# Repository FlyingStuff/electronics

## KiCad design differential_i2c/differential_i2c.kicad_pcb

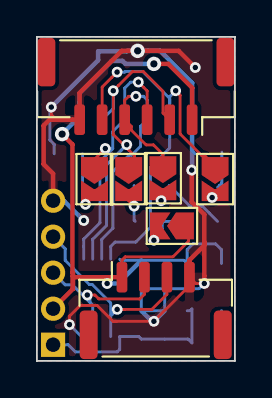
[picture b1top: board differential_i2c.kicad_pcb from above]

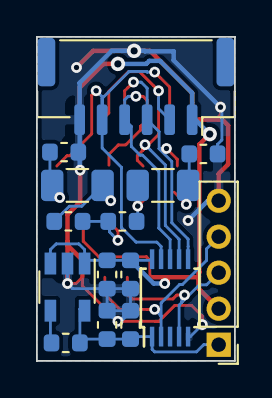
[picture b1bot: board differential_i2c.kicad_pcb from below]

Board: 2 copper layers, 11.0 x 18.0 mm, 22 parts (15 on the bottom side), 15 nets.

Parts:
C1: 1uF; C_0603_1608Metric
C2, C5: 100nF; C_0603_1608Metric
C3: 0.01uF; C_0603_1608Metric
C4: 10uF; C_0603_1608Metric
J1: I2C; JST_GH_SM04B-GHS-TB_1x04-1MP_P1.25mm_Horizontal
J2, J3: I2C_differential; JST_GH_SM06B-GHS-TB_1x06-1MP_P1.25mm_Horizontal
J4: I2C; PinHeader_1x05_P2.00mm_Vertical
JP1, JP2, JP3, JP4, JP5: NC; SolderJumper-2_P1.3mm_Open_TrianglePad1.0x1.5mm
R1, R3, R4, R6: 604; R_0603_1608Metric
R2, R5: 120; R_1206_3216Metric
U1: LT1761-3.3; TSOT-23-5
U2: PCA9615; TSSOP-10_3x3mm_P0.5mm

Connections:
+3V3: C2.1, C3.1, C4.1, J4.1, U1.5, U2.1
+5V: C1.1, C5.1, J1.1, J2.1, J3.1, J4.2, JP3.1, U1.1, U1.3, U2.10
/DI2C_SCLM: J2.3, J3.3, JP2.1, U2.6
/DI2C_SCLP: J2.2, J3.2, JP1.1, U2.7
/DI2C_SDAM: J2.5, J3.5, JP5.1, U2.9
/DI2C_SDAP: J2.4, J3.4, JP4.1, U2.8
/SCL: J1.2, J4.3, U2.4
/SDA: J1.3, J4.4, U2.2
GND: C1.2, C2.2, C4.2, C5.2, J1.4, J2.6, J3.6, J4.5, R3.2, R6.2, U1.2, U2.5
unnamed: C3.2, U1.4
unnamed: JP1.2, R1.2, R2.1
unnamed: JP2.2, R2.2, R3.1
unnamed: JP3.2, R1.1, R4.1
unnamed: JP4.2, R4.2, R5.1
unnamed: JP5.2, R5.2, R6.1

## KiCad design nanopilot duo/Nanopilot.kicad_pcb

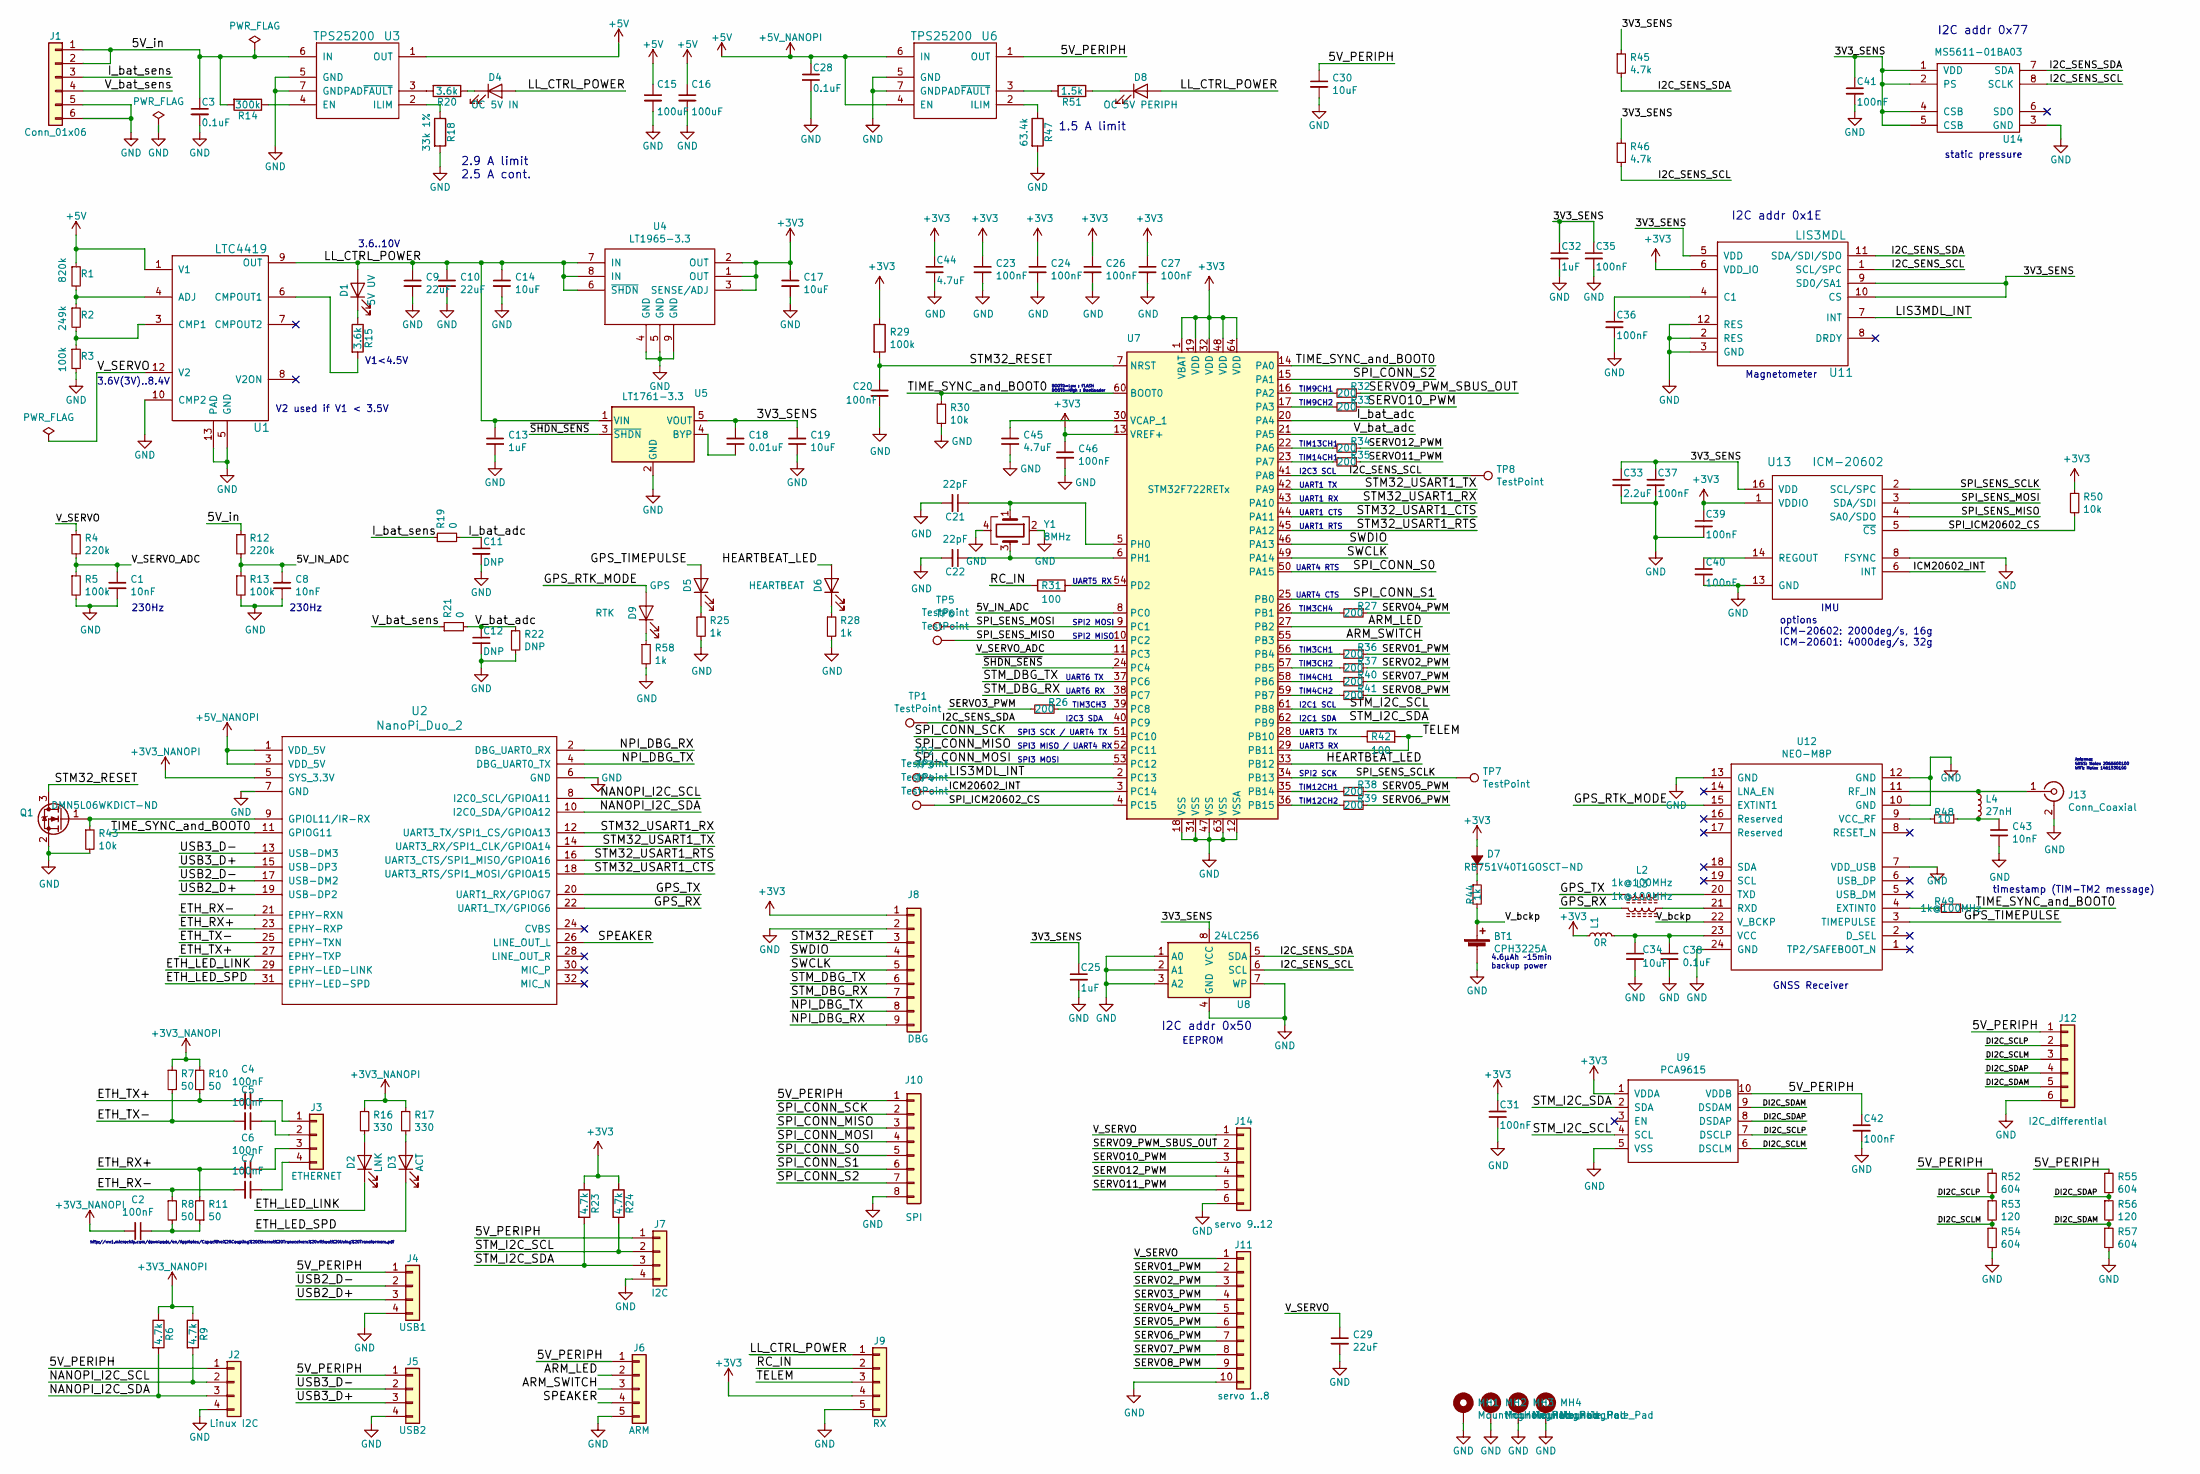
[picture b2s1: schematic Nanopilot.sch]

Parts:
BT1: CPH3225A; Seiko_supercap_CPH3225A
C1, C8, C43: 10nF; C_0603_1608Metric
C2, C4, C5, C6, C7, C20, C23, C24, C26, C27, C31, C35, C36, C37, C39, C40, C41, C42, C46: 100nF; C_0603_1608Metric
C3, C28, C38: 0.1uF; C_0603_1608Metric
C9, C10, C29: 22uF; C_0805_2012Metric
C11, C12: DNP; C_0603_1608Metric
C13, C25, C32: 1uF; C_0603_1608Metric
C14, C17, C19, C30, C34: 10uF; C_0603_1608Metric
C15, C16: 100uF; C_0805_2012Metric
C18: 0.01uF; C_0603_1608Metric
C21, C22: 22pF; C_0603_1608Metric
C33: 2.2uF; C_0603_1608Metric
C44, C45: 4.7uF; C_0603_1608Metric
D1: 5V UV; LED_0603_1608Metric
D2: LNK; LED_0603_1608Metric
D3: ACT; LED_0603_1608Metric
D4: OC 5V IN; LED_0603_1608Metric
D5: GPS; LED_0603_1608Metric
D6: HEARTBEAT; LED_0603_1608Metric
D7: RB751V40T1GOSCT-ND; D_SOD-323; part RB751V40T1GOSCT-ND
D8: OC 5V PERIPH; LED_0603_1608Metric
D9: RTK; LED_0603_1608Metric
J1: Conn_01x06; JST_GH_SM06B-GHS-TB_1x06-1MP_P1.25mm_Horizontal
J2: Linux I2C; JST_GH_SM04B-GHS-TB_1x04-1MP_P1.25mm_Horizontal
J3: ETHERNET; JST_GH_BM04B-GHS-TBT_1x04-1MP_P1.25mm_Vertical
J4: USB1; JST_GH_BM04B-GHS-TBT_1x04-1MP_P1.25mm_Vertical
J5: USB2; JST_GH_SM04B-GHS-TB_1x04-1MP_P1.25mm_Horizontal
J6: ARM; JST_GH_SM05B-GHS-TB_1x05-1MP_P1.25mm_Horizontal
J7: I2C; JST_GH_SM04B-GHS-TB_1x04-1MP_P1.25mm_Horizontal
J8: DBG; Molex_PicoBlade_53398-0971_1x09-1MP_P1.25mm_Vertical
J9: RX; JST_GH_SM05B-GHS-TB_1x05-1MP_P1.25mm_Horizontal
J10: SPI; JST_GH_BM08B-GHS-TBT_1x08-1MP_P1.25mm_Vertical
J11: servo 1..8; JST_GH_SM10B-GHS-TB_1x10-1MP_P1.25mm_Horizontal
J12: I2C_differential; JST_GH_SM06B-GHS-TB_1x06-1MP_P1.25mm_Horizontal
J13: Conn_Coaxial; U.FL_Hirose_U.FL-R-SMT-1_Vertical
J14: servo 9..12; JST_GH_SM06B-GHS-TB_1x06-1MP_P1.25mm_Horizontal
L1: 0R; L_0603_1608Metric
L2, L3: 1k@100MHz; L_0603_1608Metric; digikey 445-8672-1-ND
L4: 27nH; L_0603_1608Metric
MH1, MH2, MH3, MH4: MountingHole_Pad; MountingHole_2.2mm_M2_Pad_Via
Q1: DMN5L06WKDICT-ND; SOT-323_SC-70
R1: 820k; R_0603_1608Metric
R2: 249k; R_0603_1608Metric
R3, R5, R13, R29: 100k; R_0603_1608Metric
R4, R12: 220k; R_0603_1608Metric
R6, R9, R23, R24, R45, R46: 4.7k; R_0603_1608Metric
R7, R8, R10, R11: 50; R_0603_1608Metric
R14: 300k; R_0603_1608Metric
R15, R20: 3.6k; R_0603_1608Metric
R16, R17: 330; R_0603_1608Metric
R18: 33k 1%; R_0603_1608Metric
R19, R21: 0; R_0603_1608Metric
R22: DNP; R_0603_1608Metric
R25, R28, R44, R58: 1k; R_0603_1608Metric
R26, R27, R32, R33, R34, R35, R36, R37, R38, R39, R40, R41: 200; R_0603_1608Metric
R30, R43, R50: 10k; R_0603_1608Metric
R31, R42: 100; R_0603_1608Metric
R47: 63.4k; R_0603_1608Metric
R48: 10; R_0603_1608Metric
R49: 1k@100MHz; R_0603_1608Metric
R51: 1.5k; R_0603_1608Metric
R52, R54, R55, R57: 604; R_0603_1608Metric
R53, R56: 120; R_1206_3216Metric
TP1, TP2, TP3, TP4, TP5, TP6, TP7, TP8: TestPoint; TestPoint_Pad_D1.0mm
U1: LTC4419; MSOP-12-1EP_3x4mm_P0.65mm_EP1.65x2.85mm
U2: NanoPi_Duo_2; nanopi-duo-2
U3, U6: TPS25200; TPS25200_WSON_6
U4: LT1965-3.3; MSOP-8-1EP_3x3mm_P0.65mm_EP1.68x1.88mm
U5: LT1761-3.3; TSOT-23-5
U7: STM32F722RETx; LQFP-64_10x10mm_P0.5mm
U8: 24LC256; MSOP-8_3x3mm_P0.65mm
U9: PCA9615; TSSOP-10_3x3mm_P0.5mm
U11: LIS3MDL; LGA12R50P4X4_200X200X100
U12: NEO-M8P; ublox_NEO
U13: ICM-20602; LGA-16_3x3mm_P0.5mm_LayoutBorder3x5y-ICM-20602
U14: MS5611-01BA03; MS5611-01BA
Y1: 8MHz; Crystal_SMD_Abracon_ABM3C-4Pin_5.0x3.2mm

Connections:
+3V3: C17.1, C23.1, C24.1, C26.1, C27.1, C31.1, C39.1, C44.1, C46.1, D7.2 (A), J8.1, J9.4, L1.1, R23.1, R24.1, R29.1, R50.1, U4.1 (OUT), U4.2 (OUT), U4.3 (SENSE/ADJ), U7.1 (VBAT), U7.13 (VREF+), U7.19 (VDD), U7.32 (VDD), U7.48 (VDD), U7.64 (VDD), U9.1 (VDDA), U11.6 (VDD_IO), U13.1 (VDDIO)
+3V3_NANOPI: C2.2, R6.1, R7.1, R9.1, R10.1, R16.1, R17.1, U2.5 (SYS_3.3V)
+5V: C15.1, C16.1, C28.1, R1.1, U1.1 (V1), U2.1 (VDD_5V), U2.3 (VDD_5V), U3.1 (OUT), U6.4 (EN), U6.6 (IN)
/3V3_SENS: C18.1, C19.1, C25.1, C32.1, C33.1, C35.1, C37.1, C41.1, R45.1, R46.1, U5.5 (VOUT), U8.8 (VCC), U11.5 (VDD), U11.9 (SD0/SA1), U11.10 (CS), U13.16 (VDD), U14.1 (VDD), U14.2 (PS), U14.4 (CSB), U14.5 (CSB)
/5V_IN_ADC: C8.1, R12.2, R13.1, U7.8 (PC0)
/5V_PERIPH: C30.1, C42.1, J2.1, J4.1, J5.1, J6.1, J7.1, J10.1, J12.1, R52.1, R55.1, U6.1 (OUT), U9.10 (VDDB)
/5V_in: C3.1, J1.1, J1.2, R12.1, R14.2, U3.6 (IN)
/ARM_LED: J6.2, U7.27 (PB2)
/ARM_SWITCH: J6.3, U7.55 (PB3)
/DI2C_SCLM: J12.3, R53.2, R54.1, U9.6 (DSCLM)
/DI2C_SCLP: J12.2, R52.2, R53.1, U9.7 (DSCLP)
/DI2C_SDAM: J12.5, R56.2, R57.1, U9.9 (DSDAM)
/DI2C_SDAP: J12.4, R55.2, R56.1, U9.8 (DSDAP)
/ETH_LED_LINK: D2.1 (K), U2.29 (EPHY-LED-LINK)
/ETH_LED_SPD: D3.1 (K), U2.31 (EPHY-LED-SPD)
/ETH_RX+: C6.2, R11.2, U2.23 (EPHY-RXP)
/ETH_RX-: C7.2, R8.1, U2.21 (EPHY-RXN)
/ETH_TX+: C4.2, R10.2, U2.27 (EPHY-TXP)
/ETH_TX-: C5.2, R7.2, U2.25 (EPHY-TXN)
/GPS_RTK_MODE: D9.2 (A), U12.15 (EXTINT1)
/GPS_RX: L3.2, U2.22 (UART1_TX/GPIOG6)
/GPS_TIMEPULSE: D5.2 (A), U12.3 (TIMEPULSE)
/GPS_TX: L2.2, U2.20 (UART1_RX/GPIOG7)
/HEARTBEAT_LED: D6.2 (A), U7.33 (PB12)
/I2C_SENS_SCL: R46.2, TP8.1, U7.41 (PA8), U8.6 (SCL), U11.1 (SCL/SPC), U14.8 (SCLK)
/I2C_SENS_SDA: R45.2, TP1.1, U7.40 (PC9), U8.5 (SDA), U11.11 (SDA/SDI/SDO), U14.7 (SDA)
/ICM20602_INT: TP3.1, U7.3 (PC14), U13.6 (INT)
/I_bat_adc: C11.1, R19.2, U7.20 (PA4)
/I_bat_sens: J1.3, R19.1
/LIS3MDL_INT: TP2.1, U7.2 (PC13), U11.7 (INT)
/LL_CTRL_POWER: C9.1, C10.1, C13.1, C14.1, D1.2 (A), D4.2 (A), D8.2 (A), J9.1, U1.9 (OUT), U4.6 (~SHDN), U4.7 (IN), U4.8 (IN), U5.1 (VIN)
/NANOPI_I2C_SCL: J2.2, R9.2, U2.8 (I2C0_SCL/GPIOA11)
/NANOPI_I2C_SDA: J2.3, R6.2, U2.10 (I2C0_SDA/GPIOA12)
/NPI_DBG_RX: J8.9, U2.2 (DBG_UART0_RX)
/NPI_DBG_TX: J8.8, U2.4 (DBG_UART0_TX)
/RC_IN: J9.2, R31.1
/SERVO1_PWM: J11.2, R36.1
/SERVO2_PWM: J11.3, R37.1
/SERVO3_PWM: J11.4, R26.2
/SERVO4_PWM: J11.5, R27.1
/SERVO5_PWM: J11.6, R38.1
/SERVO6_PWM: J11.7, R39.1
/SERVO7_PWM: J11.8, R40.1
/SERVO8_PWM: J11.9, R41.1
/SERVO9_PWM_SBUS_OUT: J14.2, R32.1
/SERVO10_PWM: J14.3, R33.1
/SERVO11_PWM: J14.5, R35.1
/SERVO12_PWM: J14.4, R34.1
/SPEAKER: J6.4, U2.26 (LINE_OUT_L)
/SPI_CONN_MISO: J10.3, U7.52 (PC11)
/SPI_CONN_MOSI: J10.4, U7.53 (PC12)
/SPI_CONN_S0: J10.5, U7.50 (PA15)
/SPI_CONN_S1: J10.6, U7.25 (PB0)
/SPI_CONN_S2: J10.7, U7.15 (PA1)
/SPI_CONN_SCK: J10.2, U7.51 (PC10)
/SPI_ICM20602_CS: R50.2, TP4.1, U7.4 (PC15), U13.5 (~CS)
/SPI_SENS_MISO: TP6.1, U7.10 (PC2), U13.4 (SA0/SDO)
/SPI_SENS_MOSI: TP5.1, U7.9 (PC1), U13.3 (SDA/SDI)
/SPI_SENS_SCLK: TP7.1, U7.34 (PB13), U13.2 (SCL/SPC)
/STM32_RESET: C20.1, J8.3, Q1.3 (D), R29.2, U7.7 (NRST)
/STM32_USART1_CTS: U2.18 (UART3_RTS/SPI1_MOSI/GPIOA15), U7.44 (PA11)
/STM32_USART1_RTS: U2.16 (UART3_CTS/SPI1_MISO/GPIOA16), U7.45 (PA12)
/STM32_USART1_RX: U2.12 (UART3_TX/SPI1_CS/GPIOA13), U7.43 (PA10)
/STM32_USART1_TX: U2.14 (UART3_RX/SPI1_CLK/GPIOA14), U7.42 (PA9)
/STM_DBG_RX: J8.7, U7.38 (PC7)
/STM_DBG_TX: J8.6, U7.37 (PC6)
/STM_I2C_SCL: J7.2, R24.2, U7.61 (PB8), U9.4 (SCL)
/STM_I2C_SDA: J7.3, R23.2, U7.62 (PB9), U9.2 (SDA)
/SWCLK: J8.5, U7.49 (PA14)
/SWDIO: J8.4, U7.46 (PA13)
/TELEM: J9.3, R42.2, U7.29 (PB11)
/TIME_SYNC_and_BOOT0: R30.1, R49.1, U2.11 (GPIOG11), U7.14 (PA0), U7.60 (BOOT0)
/USB2_D+: J4.3, U2.19 (USB-DP2)
/USB2_D-: J4.2, U2.17 (USB-DM2)
/USB3_D+: J5.3, U2.15 (USB-DP3)
/USB3_D-: J5.2, U2.13 (USB-DM3)
/V_SERVO: C29.1, J11.1, J14.1, R4.1, U1.12 (V2)
/V_SERVO_ADC: C1.1, R4.2, R5.1, U7.11 (PC3)
/V_bat_adc: C12.1, R21.2, R22.1, U7.21 (PA5)
/V_bat_sens: J1.4, R21.1
/V_bckp: BT1.1 (+), R44.2, U12.22 (V_BCKP)
/~SHDN_SENS: U5.3 (~SHDN), U7.24 (PC4)
GND: BT1.2 (-), C1.2, C3.2, C8.2, C9.2, C10.2, C11.2, C12.2, C13.2, C14.2, C15.2, C16.2, C17.2, C19.2, C20.2, C21.2, C22.2, C23.2, C24.2, C25.2, C26.2, C27.2, C28.2, C29.2, C30.2, C31.2, C32.2, C33.2, C34.2, C35.2, C36.2, C37.2, C38.2, C39.2, C40.2, C41.2, C42.2, C43.2, C44.2, C45.2, C46.2, J1.5, J1.6, J2.4, J4.4, J5.4, J6.5, J7.4, J8.2, J9.5, J10.8, J11.10, J12.6, J13.2 (Ext), J14.6, MH1.1, MH2.1, MH3.1, MH4.1, Q1.2 (S), R3.2, R5.2, R13.2, R18.2, R22.2, R25.2, R28.2, R30.2, R43.2, R47.2, R54.2, R57.2, R58.2, U1.5 (GND), U1.10 (CMP2), U1.13 (PAD), U2.6 (GND), U2.7 (GND), U3.5 (GND), U3.7 (GNDPAD), U4.4 (GND), U4.5 (GND), U4.9 (GND), U5.2 (GND), U6.5 (GND), U6.7 (GNDPAD), U7.12 (VSSA), U7.18 (VSS), U7.31 (VSS), U7.47 (VSS), U7.63 (VSS), U8.1 (A0), U8.2 (A1), U8.3 (A2), U8.4 (GND), U8.7 (WP), U9.5 (VSS), U11.2 (RES), U11.3 (GND), U11.12 (RES), U12.7 (VDD_USB), U12.10 (GND), U12.12 (GND), U12.13 (GND), U12.24 (GND), U13.8 (FSYNC), U13.9 (GND), U13.10 (GND), U13.11 (GND), U13.12 (GND), U13.13 (GND), U13.15 (GND), U14.3 (GND), Y1.2, Y1.4
unnamed: C2.1, R8.2, R11.1
unnamed: C4.1, J3.1
unnamed: C5.1, J3.2
unnamed: C6.1, J3.3
unnamed: C7.1, J3.4
unnamed: C18.2, U5.4 (BYP)
unnamed: C21.1, U7.5 (PH0), Y1.1
unnamed: C22.1, U7.6 (PH1), Y1.3
unnamed: C34.1, C38.1, L1.2, U12.23 (VCC)
unnamed: C36.1, U11.4 (C1)
unnamed: C40.1, U13.14 (REGOUT)
unnamed: C43.1, L4.2, R48.1
unnamed: C45.1, U7.30 (VCAP_1)
unnamed: D1.1 (K), R15.1
unnamed: D2.2 (A), R16.2
unnamed: D3.2 (A), R17.2
unnamed: D4.1 (K), R20.1
unnamed: D5.1 (K), R25.1
unnamed: D6.1 (K), R28.1
unnamed: D7.1 (K), R44.1
unnamed: D8.1 (K), R51.1
unnamed: D9.1 (K), R58.1
unnamed: J13.1 (In), L4.1, U12.11 (RF_IN)
unnamed: L2.1, U12.20 (TXD)
unnamed: L3.1, U12.21 (RXD)
unnamed: Q1.1 (G), R43.1, U2.9 (GPIOL11/IR-RX)
unnamed: R1.2, R2.1, U1.4 (ADJ)
unnamed: R2.2, R3.1, U1.3 (CMP1)
unnamed: R14.1, U3.4 (EN)
unnamed: R15.2, U1.6 (CMPOUT1)
unnamed: R18.1, U3.2 (ILIM)
unnamed: R20.2, U3.3 (~FAULT)
unnamed: R26.1, U7.39 (PC8)
unnamed: R27.2, U7.26 (PB1)
unnamed: R31.2, U7.54 (PD2)
unnamed: R32.2, U7.16 (PA2)
unnamed: R33.2, U7.17 (PA3)
unnamed: R34.2, U7.22 (PA6)
unnamed: R35.2, U7.23 (PA7)
unnamed: R36.2, U7.56 (PB4)
unnamed: R37.2, U7.57 (PB5)
unnamed: R38.2, U7.35 (PB14)
unnamed: R39.2, U7.36 (PB15)
unnamed: R40.2, U7.58 (PB6)
unnamed: R41.2, U7.59 (PB7)
unnamed: R42.1, U7.28 (PB10)
unnamed: R47.1, U6.2 (ILIM)
unnamed: R48.2, U12.9 (VCC_RF)
unnamed: R49.2, U12.4 (EXTINT0)
unnamed: R51.2, U6.3 (~FAULT)

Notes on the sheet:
2.9 A limit 2.5 A cont.
UART5 RX
230Hz
3.6..10V
timestamp (TIM-TM2 message)
BOOT0=Low : FLASH BOOT0=High : Bootloader
I2C addr 0x1E
I2C addr 0x77
I2C addr 0x50
Magnetometer
IMU
static pressure
GNSS Receiver
EEPROM
http://ww1.microchip.com/downloads/en/AppNotes/Capacitive%20Coupling%20Ethernet%20Transceivers%20without%20Using%20Transformers.pdf
UART3 TX
UART3 RX
3.6V(3V)..8.4V
UART6 RX
UART6 TX
I2C3 SDA
I2C3 SCL
I2C1 SCL
I2C1 SDA
UART1 TX
UART1 RX
UART1 CTS
UART1 RTS
SPI2 MOSI
SPI2 MISO
SPI2 SCK
SPI3 SCK / UART4 TX
SPI3 MISO / UART4 RX
SPI3 MOSI
UART4 RTS
UART4 CTS
TIM3CH1
TIM3CH2
TIM3CH4
TIM3CH3

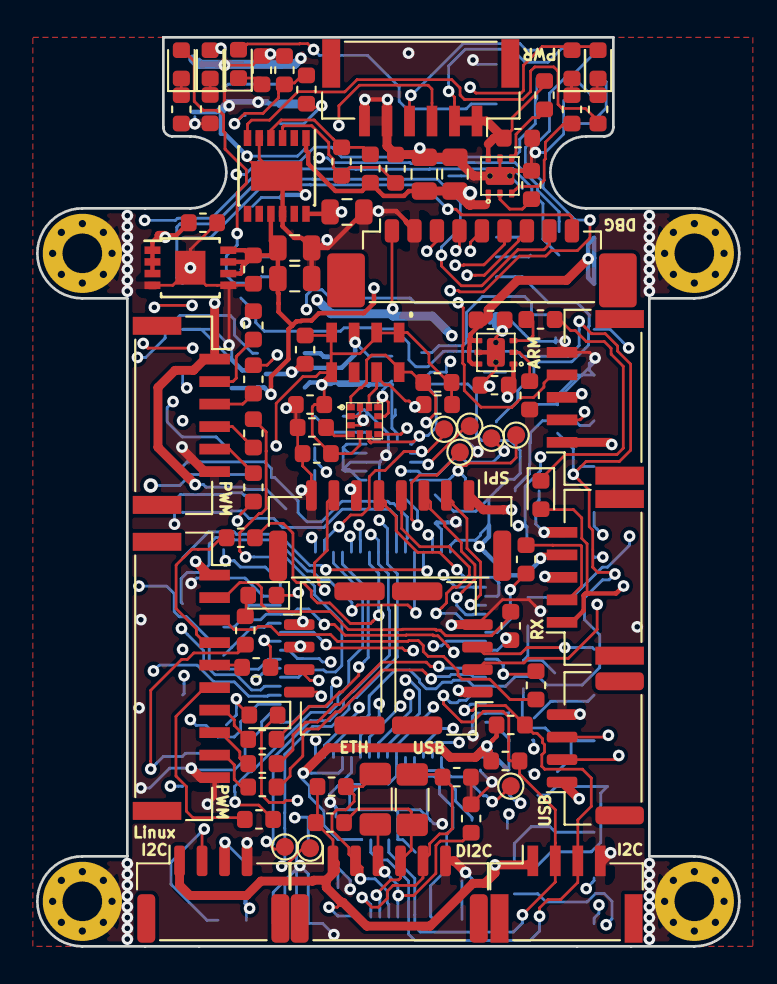
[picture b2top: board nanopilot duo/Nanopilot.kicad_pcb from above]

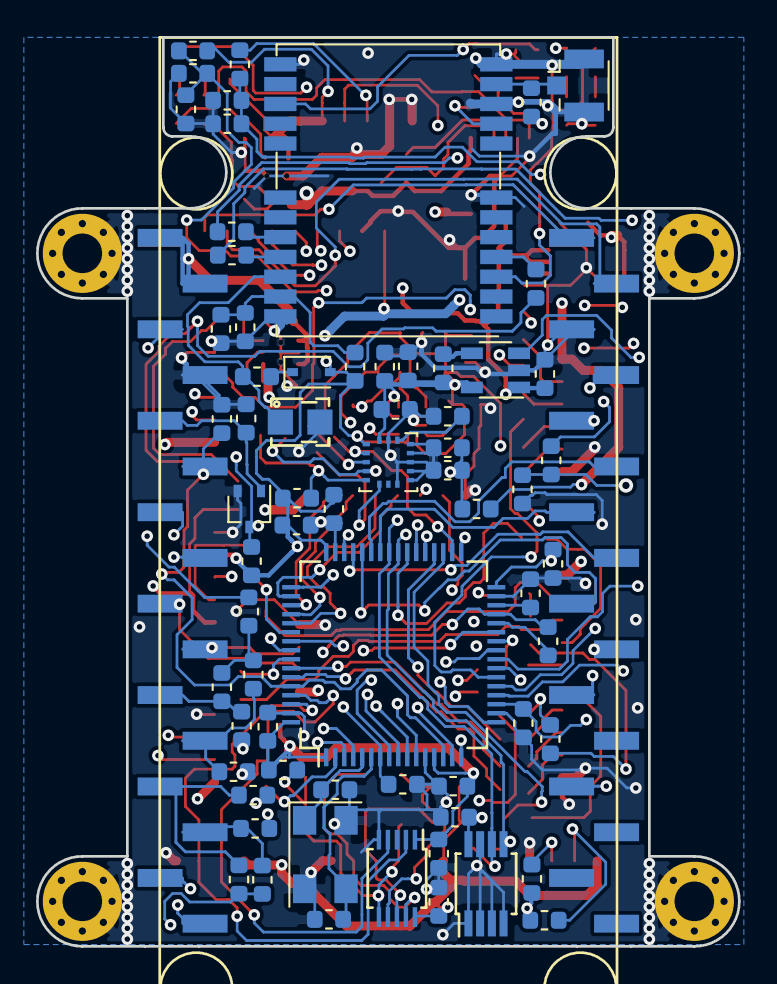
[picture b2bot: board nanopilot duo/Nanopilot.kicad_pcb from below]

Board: 4 copper layers, 39.0 x 50.5 mm, 159 parts (68 on the bottom side), 133 nets.

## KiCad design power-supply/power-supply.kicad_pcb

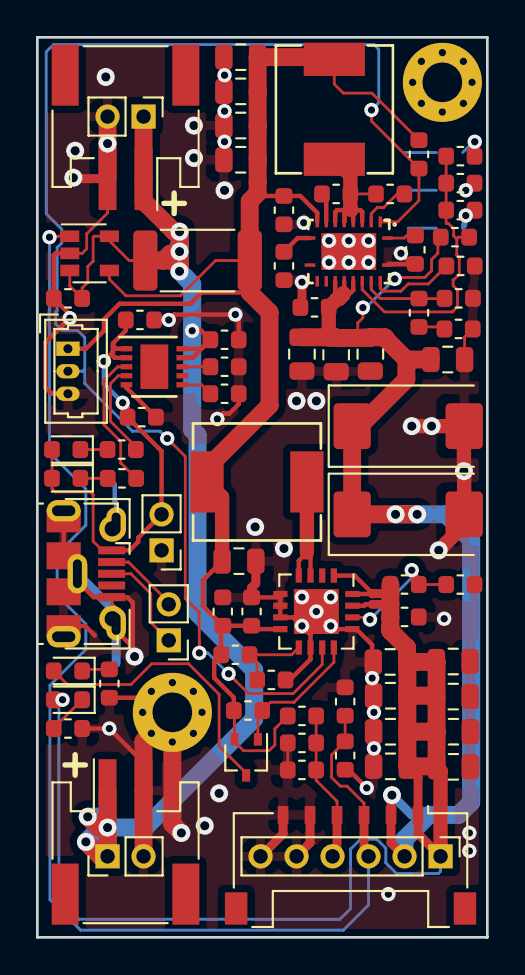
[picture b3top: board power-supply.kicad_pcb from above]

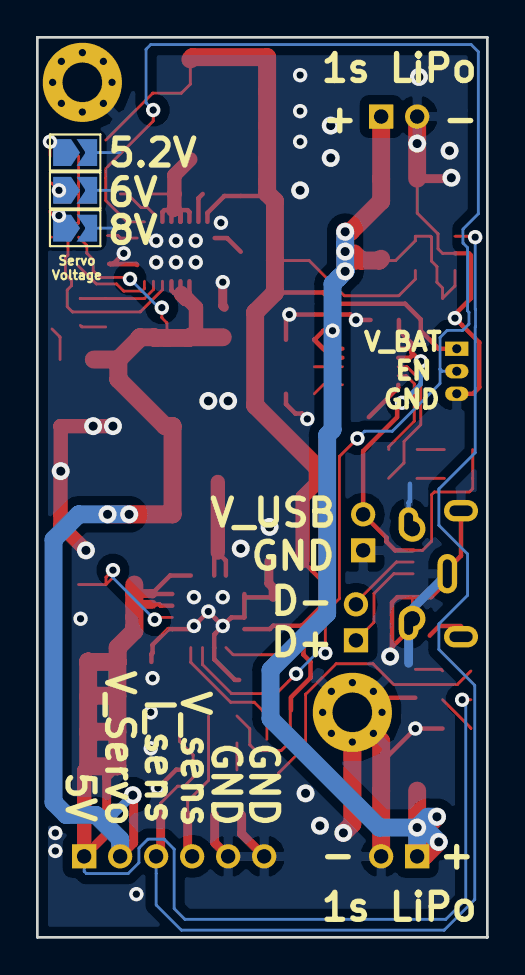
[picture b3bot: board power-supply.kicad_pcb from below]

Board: 2 copper layers, 25.0 x 50.0 mm, 84 parts (3 on the bottom side), 36 nets.

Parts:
C1, C6, C14, C17: 1uF; C_0603_1608Metric
C2, C4: 100nF; C_0603_1608Metric
C3, C11: 10uF; C_0603_1608Metric
C5, C7, C8, C21, C27, C28, C29, C30, C31, C32, C33, C34, C35: 47uF 10V; C_0805_2012Metric
C9: 10nF; C_0603_1608Metric
C10, C12, C13: 0.1uF; C_0603_1608Metric
C15: 47nF; C_0603_1608Metric
C16: 2.2uF; C_0603_1608Metric
C18: 36pF; C_0603_1608Metric
C19: 680pF; C_0603_1608Metric
C20, C22, C23, C24: 22uF; C_0805_2012Metric
C25, C26: 220uF 16V; CP_EIA-7343-31_Kemet-D
D1, D4: Green; LED_0603_1608Metric
D2: Orange; LED_0603_1608Metric
D3: Red; LED_0603_1608Metric
J1, J5: SolderPins; PinHeader_1x02_P2.00mm_Vertical
J2: USB_B_Micro; USB_Micro-B_Molex-105133-0001_or_105017-0001
J3: BATT_B; JST_PH_S2B-PH-SM4-TB_1x02-1MP_P2.00mm_Horizontal
J4: BATT_A; JST_PH_S2B-PH-SM4-TB_1x02-1MP_P2.00mm_Horizontal
J6: switch; Molex_PicoBlade_53047-0610_1x03_P1.25mm_Vertical
J7: Power; Molex_Pico-Lock_504050-0691_1x06-1MP_P1.50mm_Horizontal
J8: BATT_B_solder; PinHeader_1x02_P2.00mm_Vertical
J9: BATT_A_solder; PinHeader_1x02_P2.00mm_Vertical
J10: Power_solder; PinHeader_1x06_P2.00mm_Vertical
JP1: 5.2V; SolderJumper-2_P1.3mm_Open_TrianglePad1.0x1.5mm
JP2: 6V; SolderJumper-2_P1.3mm_Open_TrianglePad1.0x1.5mm
JP3: 8V; SolderJumper-2_P1.3mm_Open_TrianglePad1.0x1.5mm
L1: 1.5uH SPM6530T-1R5M100; L-TDK-SPM6530
L2: 6.8uH 4A SPM6530T-6R8M; L-TDK-SPM6530
MH1, MH2: MountingHole_Pad; MountingHole_2.2mm_M2_Pad_Via
Q1: Q_PMOS_GSD; SOT-323_SC-70
R1, R2, R18: 470; R_0603_1608Metric
R3: 0.020 (2W); R_2512_6332Metric
R4, R7: 10k; R_0603_1608Metric
R5: 1M; R_0603_1608Metric
R6, R22: 1k; R_0603_1608Metric
R8, R9, R14, R16: 220k; R_0603_1608Metric
R10: 249k; R_0603_1608Metric
R11, R13: 1.87M; R_0603_1608Metric
R12: 340k; R_0603_1608Metric
R15: 36.5k; R_0603_1608Metric
R17: 100k; R_0603_1608Metric
R19: 182k; R_0603_1608Metric
R20: 604k; R_0603_1608Metric
R21: 150k; R_0603_1608Metric
R23: 107k; R_0603_1608Metric
U1: INA139; SOT-23-5
U2: MCP73833; DFN-10-1EP_3x3mm_P0.5mm_EP1.55x2.48mm
U3: TPS61088; VQFN-20-4.5x3.5
U4: TPS61030; QFN-16-1EP_4x4mm_P0.65mm_EP2.5x2.5mm

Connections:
+5V: C16.1, C21.1, C27.1, C28.1, C29.1, C30.1, C31.1, C32.1, C33.1, D4.2, J7.1, J10.1, R13.1, U4.1, U4.15, U4.16
/I_sens: C4.1, J7.3, J10.3, R4.1, U1.1
/PWR_EN: J6.2, R5.2, U3.2, U4.11
/V_BAT: C2.1, C6.1, J3.1, J4.1, J8.1, J9.1, R3.2, U1.3, U1.5, U2.9, U2.10
/V_BAT_LOAD: C5.1, C7.1, C8.1, C10.1, C11.1, C12.1, C34.1, C35.1, J6.1, L1.1, L2.1, Q1.2, R3.1, R5.1, R8.1, R11.1, R16.1, U1.4, U3.9, U4.8
/V_SERVO: C17.1, C20.1, C22.1, C23.1, C24.1, C25.1, C26.1, J7.2, J10.2, R20.1, U3.14, U3.15, U3.16
/V_USB: C1.1, C3.1, D1.2, D2.2, J1.2, J2.1, U2.1, U2.2
/V_sens: C9.1, J7.4, J10.4, R8.2, R9.1
GND: C1.2, C2.2, C3.2, C4.2, C5.2, C6.2, C7.2, C8.2, C9.2, C10.2, C11.2, C12.2, C14.2, C15.2, C16.2, C17.2, C18.2, C19.2, C20.2, C21.2, C22.2, C23.2, C24.2, C25.2, C26.2, C27.2, C28.2, C29.2, C30.2, C31.2, C32.2, C33.2, C34.2, C35.2, J1.1, J2.5, J2.6, J3.2, J4.2, J6.3, J7.5, J7.6, J8.2, J9.2, J10.5, J10.6, JP1.2, JP2.2, JP3.2, MH1.1, MH2.1, R4.2, R6.2, R7.2, R9.2, R12.2, R14.2, R17.2, R18.2, R22.2, U1.2, U2.5, U3.20, U3.21, U4.5, U4.6, U4.7, U4.10, U4.13, U4.17
unnamed: C13.1, L1.2, R10.1, U3.4, U3.5, U3.6, U3.7
unnamed: C13.2, U3.8
unnamed: C14.1, U3.1
unnamed: C15.1, U3.10
unnamed: C18.1, R15.1, U3.18
unnamed: C19.1, R15.2
unnamed: D1.1, R1.1
unnamed: D2.1, R2.1
unnamed: D3.1, R18.1
unnamed: D3.2, Q1.3
unnamed: D4.1, R22.1
unnamed: J2.2, J5.2
unnamed: J2.3, J5.1
unnamed: JP1.1, R19.2
unnamed: JP2.1, R21.2
unnamed: JP3.1, R23.2
unnamed: L2.2, U4.3, U4.4
unnamed: Q1.1, R16.2, U4.12
unnamed: R1.2, U2.4
unnamed: R2.2, U2.3
unnamed: R6.1, U2.6
unnamed: R7.1, U2.8
unnamed: R10.2, U3.3
unnamed: R11.2, R12.1, U4.9
unnamed: R13.2, R14.1, U4.14
unnamed: R17.1, U3.19
unnamed: R19.1, R20.2, R21.1, R23.1, U3.17

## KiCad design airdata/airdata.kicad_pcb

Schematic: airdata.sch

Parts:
C1, C2, C3, C5, C7: 100nF; C_0603_1608Metric
C4: 1uF; C_0603_1608Metric
C6: 0.01uF; C_0603_1608Metric
C8: 10uF; C_0603_1608Metric
J1, J2: I2C; JST_GH_BM04B-GHS-TBT_1x04-1MP_P1.25mm_Vertical
R1: 0; R_0603_1608Metric
R2: 1.2k; R_0603_1608Metric
R3: 2.7k; R_0603_1608Metric
U1, U3, U6: SDP32; SDP3x
U2: MS5611-01BA03; MS5611-01BA
U4: LT1761-3.3; TSOT-23-5
U5: HSCMRRN001PD2A3; HSCMRRN001PD2A3-side-mount

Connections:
+3V3: C1.1, C2.1, C3.1, C5.1, C6.1, C7.1, C8.1, U1.7, U2.1, U2.2, U2.4, U2.5, U3.7, U4.5 (VOUT), U5.2, U6.7
+5V: C4.1, J1.1, J2.1, U4.1 (VIN), U4.3 (~SHDN)
/SCL: J1.2, J2.2, U1.5, U2.8, U3.5, U5.4, U6.5
/SDA: J1.3, J2.3, U1.8, U2.7, U3.8, U5.3, U6.8
GND: C1.2, C2.2, C3.2, C4.2, C5.2, C7.2, C8.2, J1.4, J2.4, R1.2, R2.2, R3.2, U1.1, U1.2, U1.3, U1.6, U1.10, U1.11, U2.3, U3.1, U3.2, U3.3, U3.6, U3.10, U3.11, U4.2 (GND), U5.1, U6.1, U6.2, U6.3, U6.6, U6.10, U6.11
unnamed: C6.2, U4.4 (BYP)
unnamed: R1.1, U1.9
unnamed: R2.1, U3.9
unnamed: R3.1, U6.9

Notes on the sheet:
I2C addr 0k 0x21 1.2k 0x22 2.7k 0x23
addr 0x77
alpha
beta
dynamic pressure
static pressure
up to 380km/h (6890Pa)
I2C Address 0x28
SDP32 (125Pa) up to 50km/h SDP31 (500Pa) up to 100km/h SDP33 (1500Pa) up to 180km/h

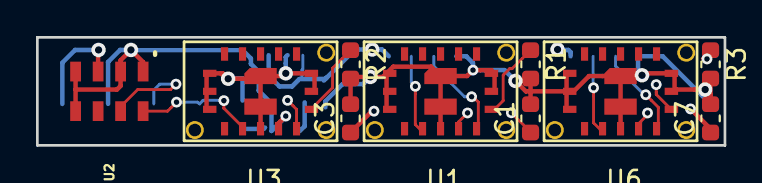
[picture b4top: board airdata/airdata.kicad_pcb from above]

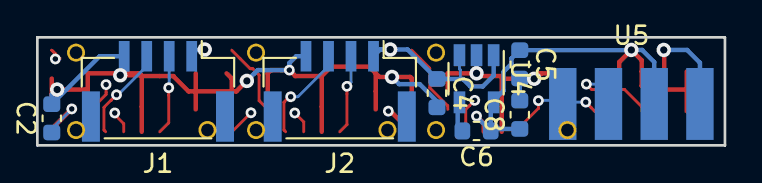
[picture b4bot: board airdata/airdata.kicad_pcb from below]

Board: 4 copper layers, 38.2 x 6.0 mm, 19 parts (9 on the bottom side), 9 nets.
